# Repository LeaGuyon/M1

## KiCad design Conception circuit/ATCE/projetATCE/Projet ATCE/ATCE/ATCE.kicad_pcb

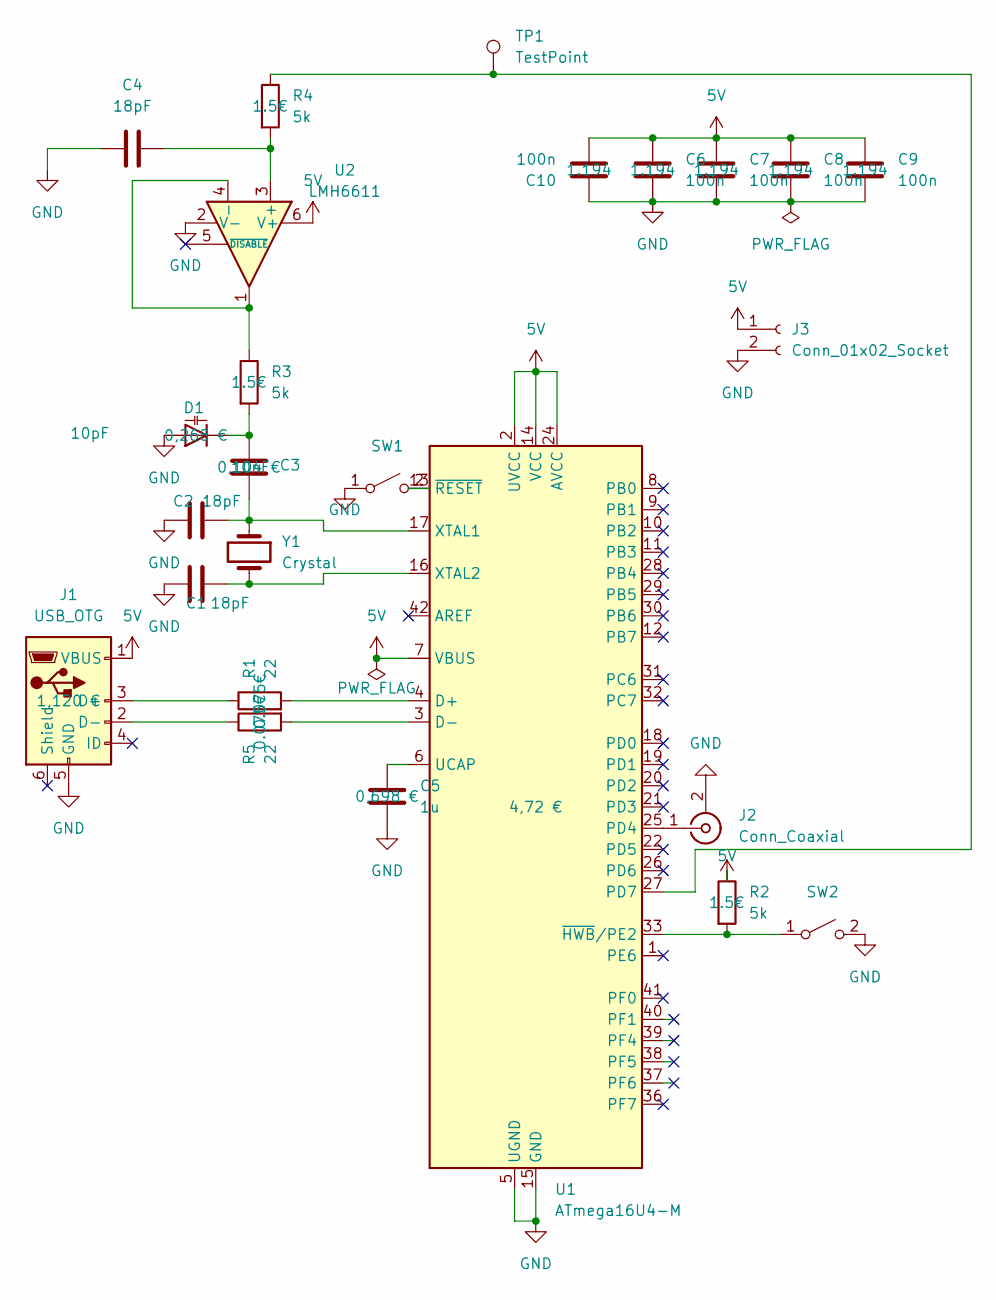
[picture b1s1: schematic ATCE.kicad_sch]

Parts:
C1, C2, C4: 18pF; C_0805_2012Metric_Pad1.18x1.45mm_HandSolder
C3: 10nF; C_0805_2012Metric_Pad1.18x1.45mm_HandSolder
C5: 1u; C_0805_2012Metric_Pad1.18x1.45mm_HandSolder
C6, C7, C8, C9, C10: 100n; C_0805_2012Metric_Pad1.18x1.45mm_HandSolder
D1: 10pF; D_SOD-323
J1: USB_OTG; USB_Micro-B_Molex-105017-0001
J2: Conn_Coaxial; SMA_Amphenol_132134-14_Vertical
J3: Conn_01x02_Socket; PinHeader_1x02_P2.54mm_Vertical
R1, R5: 22; R_0805_2012Metric_Pad1.20x1.40mm_HandSolder
R2, R3, R4: 5k; R_0805_2012Metric_Pad1.20x1.40mm_HandSolder
SW1, SW2: SW_PUSH_6mm
TP1: TestPoint; TestPoint_Pad_D2.0mm
U1: ATmega16U4-M; QFN-44-1EP_7x7mm_P0.5mm_EP5.2x5.2mm
U2: LMH6611; TSOT-23-6
Y1: Crystal; Crystal_HC49-U_Vertical

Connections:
5V: C6.1, C7.1, C8.1, C9.1, C10.2, J1.1 (VBUS), J3.1, R2.1, U1.2 (UVCC), U1.7 (VBUS), U1.14 (VCC), U1.24 (AVCC), U1.34 (VCC), U1.44 (AVCC), U2.6 (V+)
GND: C1.2, C2.1, C4.1, C5.2, C6.2, C7.2, C8.2, C9.2, C10.1, D1.2 (A), J1.5 (GND), J2.2 (Ext), J3.2, SW1.1 (A), SW2.2 (B), U1.5 (UGND), U1.15 (GND), U1.23 (GND), U1.35 (GND), U1.43 (GND), U1.45 (GND), U2.2 (V-)
unnamed: C3.1, D1.1 (K), R3.2
unnamed: J1.3 (D+), R1.1
unnamed: J1.2 (D-), R5.1
unnamed: J2.1 (In), U1.25 (PD4)
unnamed: SW1.2 (B), U1.13 (~RESET)
unnamed: R2.2, SW2.1 (A), U1.33 (~HWB/PE2)
unnamed: R1.2, U1.4 (D+)
unnamed: R5.2, U1.3 (D-)
unnamed: R4.1, TP1.1, U1.27 (PD7)
unnamed: C5.1, U1.6 (UCAP)
unnamed: C2.2, C3.2, U1.17 (XTAL1), Y1.1
unnamed: C1.1, U1.16 (XTAL2), Y1.2
unnamed: C4.2, R4.2, U2.3 (+)
unnamed: R3.1, U2.1, U2.4 (-)

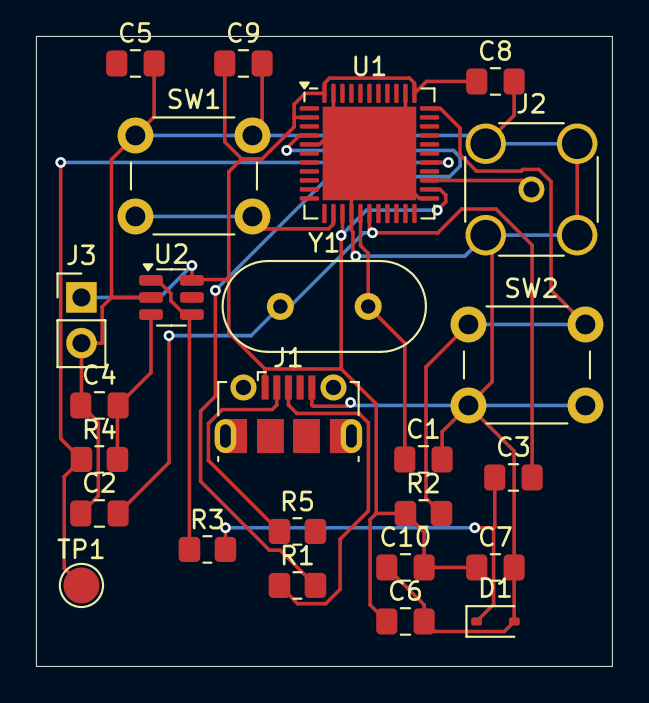
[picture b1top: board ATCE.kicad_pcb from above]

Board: 2 copper layers, 32.0 x 35.0 mm, 25 parts (0 on the bottom side), 16 nets.

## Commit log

2025-09-12 test de push sur git
2025-09-13 tp2 codes makefile
2025-09-15 Create testGit.txt
    test
2025-09-15 ajout blink elf
2025-09-15 code C du programme blink
2025-09-15 push de toute les extensions de blink
2025-09-15 projet S6 et TP conception Master
